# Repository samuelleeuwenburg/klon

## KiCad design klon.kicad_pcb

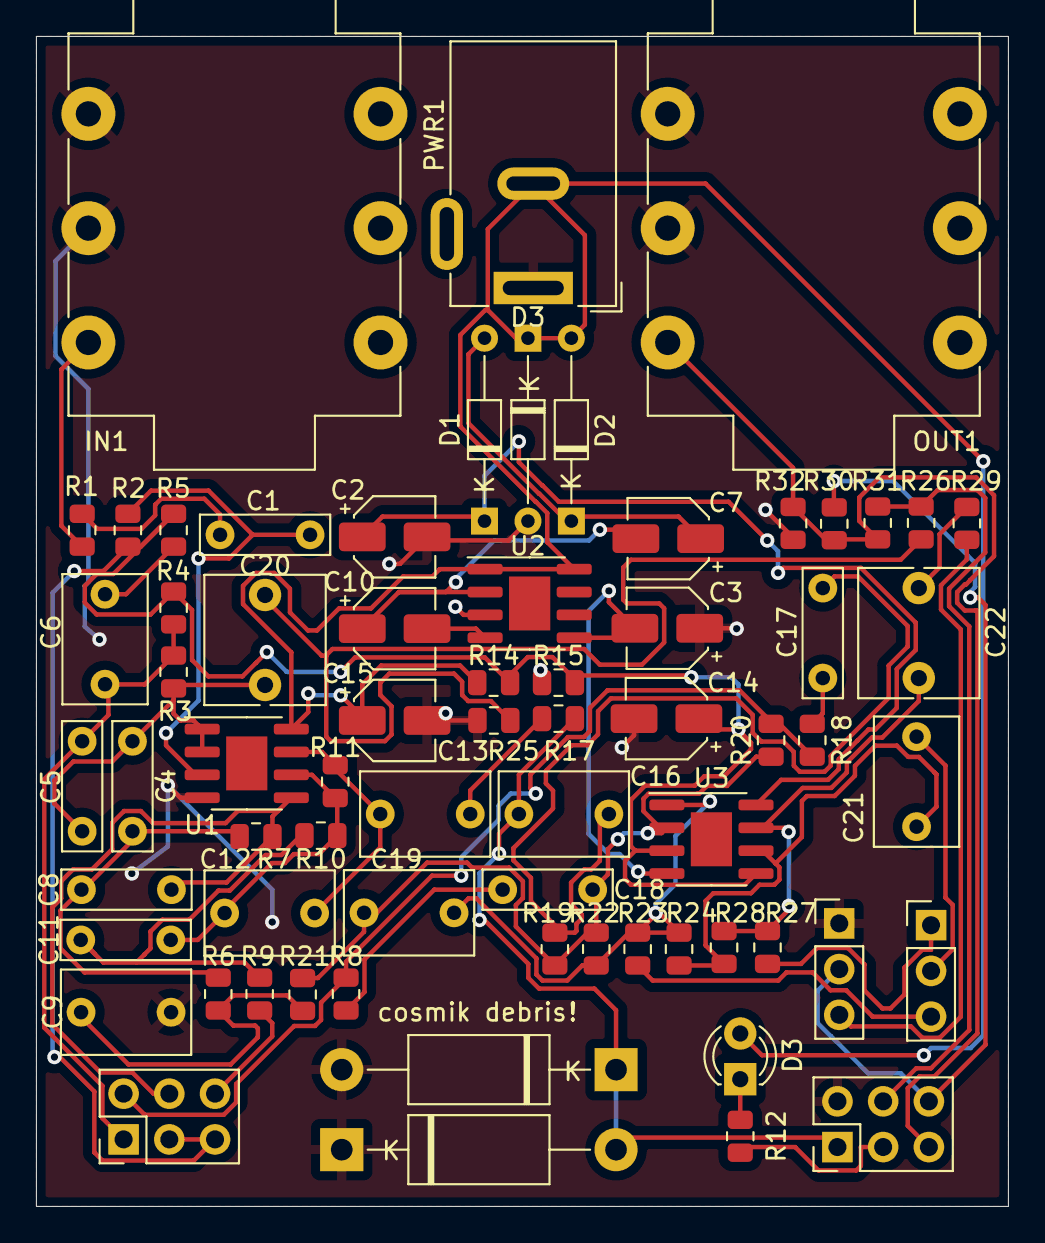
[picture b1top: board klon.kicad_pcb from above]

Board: 2 copper layers, 54.0 x 65.0 mm, 68 parts (0 on the bottom side), 42 nets.

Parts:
!: 1N34A; D_DO-15_P15.24mm_Horizontal
C1, C4: 0.1u; C_Rect_L7.0mm_W2.0mm_P5.00mm
C2, C3, C7, C10: 1u; CP_Elec_4x4.5
C5, C8: 0.068u; C_Rect_L7.0mm_W2.0mm_P5.00mm
C6: 0.39u; C_Rect_L7.0mm_W4.5mm_P5.00mm
C9, C13, C16: 1u; C_Rect_L7.0mm_W4.5mm_P5.00mm
C11: 0.082u; C_Rect_L7.0mm_W2.0mm_P5.00mm
C12: 390p; C_Rect_L7.0mm_W4.5mm_P5.00mm
C14, C15: 47u; CP_Elec_4x4.5
C17: 2200p; C_Rect_L7.0mm_W2.0mm_P5.00mm
C18: 0.027u; C_Rect_L7.0mm_W2.0mm_P5.00mm
C19: 820p; C_Rect_L7.0mm_W4.5mm_P5.00mm
C20, C22: 4.7u; C_Rect_L7.0mm_W6.5mm_P5.00mm
C21: 3900p; C_Rect_L7.0mm_W4.5mm_P5.00mm
D1, D2: 1N4001; D_DO-34_SOD68_P10.16mm_Horizontal
D3: LED; LED_D3.0mm_Clear
D3#2: 1N4742; D_DO-34_SOD68_P10.16mm_Horizontal
GAIN: 100K; PinHeader_2x03_P2.54mm_Vertical
IN1: AudioJack3; Jack_6.35mm_Neutrik_NMJ6HFD2_Horizontal
OUT1: AudioJack3; Jack_6.35mm_Neutrik_NMJ6HFD2_Horizontal
PWR1: Barrel_Jack; BarrelJack_Wuerth_6941xx301002
R1, R7: 10K; R_0805_2012Metric
R2: 1M; R_0805_2012Metric
R3: 5K1; R_0805_2012Metric
R4, R6: 1K5; R_0805_2012Metric
R5, R17: 1K; R_0805_2012Metric
R8, R10: 15K; R_0805_2012Metric
R9: 2K; R_0805_2012Metric
R11: 422K; R_0805_2012Metric
R12: 3K9; R_0805_2012Metric
R14, R15, R20: 27K; R_0805_2012Metric
R18: 22K; R_0805_2012Metric
R19: 47K; R_0805_2012Metric
R21: 12K; R_0805_2012Metric
R22: 392K; R_0805_2012Metric
R23: 1K8; R_0805_2012Metric
R24, R25, R28, R32: 100K; R_0805_2012Metric
R26, R29: 560; R_0805_2012Metric
R27: 4K7; R_0805_2012Metric
R30, R31: 68K; R_0805_2012Metric
SW: SW_DPDT_x2; PinHeader_2x03_P2.54mm_Vertical
TONE: 10K; PinHeader_1x03_P2.54mm_Vertical
U1, U3: TL072; SOIC-8-1EP_3.9x4.9mm_P1.27mm_EP2.29x3mm
U2: LTC1044A; SOIC-8-1EP_3.9x4.9mm_P1.27mm_EP2.29x3mm
VOL: 10K; PinHeader_1x03_P2.54mm_Vertical
cosmik debris: 1N34A; D_DO-15_P15.24mm_Horizontal

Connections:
+9V: C15.1, D2.2 (A), D3.2 (A), D3#2.1 (K), PWR1.2, R14.1, U1.8 (V+), U2.1 (BOOST), U2.8 (V+)
/+4.5V: C14.1, GAIN.3, GAIN.5, R2.2, R4.2, R5.2, R14.2, R15.1, U3.3 (+), U3.5 (+)
/+16.2V: C2.1, D1.1 (K), U3.8 (V+)
/-8.6V: C3.2, U2.5 (VOUT), U3.4 (V-)
GND: !.2 (A), C2.2, C3.1, C9.1, C14.2, C15.2, D3#2.2 (A), IN1.R, IN1.S, OUT1.R, OUT1.S, PWR1.1, R15.2, R25.1, R32.2, SW.2 (B), U1.4 (V-), U2.3 (GND), VOL.1, cosmik debris.1 (K)
unnamed: C1.1, R2.1, U1.3 (+)
unnamed: C1.2, R1.1
unnamed: C4.1, C8.2, R6.2, R7.2
unnamed: C5.2, C6.2, GAIN.1, R3.2, R4.1
unnamed: C6.1, R5.1
unnamed: C7.1, D1.2 (A), D2.1 (K)
unnamed: C8.1, GAIN.4, R7.1, U1.5 (+)
unnamed: C9.2, R6.1, R8.2
unnamed: C7.2, C10.1, U2.2 (CAP+)
unnamed: C10.2, U2.4 (CAP-)
unnamed: C11.1, C12.2, R10.1, R11.2, U1.6 (-)
unnamed: C11.2, R9.2, R10.2
unnamed: C12.1, C13.2, R11.1, U1.7
unnamed: C13.1, R17.2
unnamed: C16.1, C17.1, R19.2
unnamed: !.1 (K), C16.2, R17.1, SW.1 (A), cosmik debris.2 (A)
unnamed: C17.2, R18.1
unnamed: C18.1, C19.2, R8.1, R19.1, R20.1, R22.2, U3.2 (-)
unnamed: C18.2, R21.1
unnamed: C19.1, R22.1, R23.2, R24.2, U3.1
unnamed: C4.2, C5.1, C20.1, R3.1, U1.1, U1.2 (-)
unnamed: C20.2, R25.2, R26.2
unnamed: C21.1, R24.1, R28.2, U3.6 (-)
unnamed: C21.2, TONE.2
unnamed: C22.1, R29.2
unnamed: C22.2, R27.1, R28.1, U3.7
unnamed: D3.1 (K), R12.1
unnamed: GAIN.2, R18.2, R20.2, R21.2
unnamed: GAIN.6, R9.1
unnamed: IN1.T, R1.2
unnamed: OUT1.T, R30.1, R31.1, R32.1, SW.5 (B)
unnamed: R12.2, SW.3 (C)
unnamed: R23.1, TONE.3
unnamed: R26.1, R31.2, SW.4 (A)
unnamed: R27.2, TONE.1
unnamed: R29.1, VOL.3
unnamed: R30.2, SW.6 (C), VOL.2

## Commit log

2021-06-26 update footprints, values
2021-07-02 update footprints, add bypass LED circuit
2021-07-03 add PCB layout
2021-07-04 add custom models, change pcb board layout
2021-07-04 optimize board to new dimensions
2021-07-06 add pcb traces
2021-07-14 fix power polarity, new PCB layout
2021-07-28 update pcb layout
2021-12-30 update to kicad 6.0, use SMD resistors, ICs
